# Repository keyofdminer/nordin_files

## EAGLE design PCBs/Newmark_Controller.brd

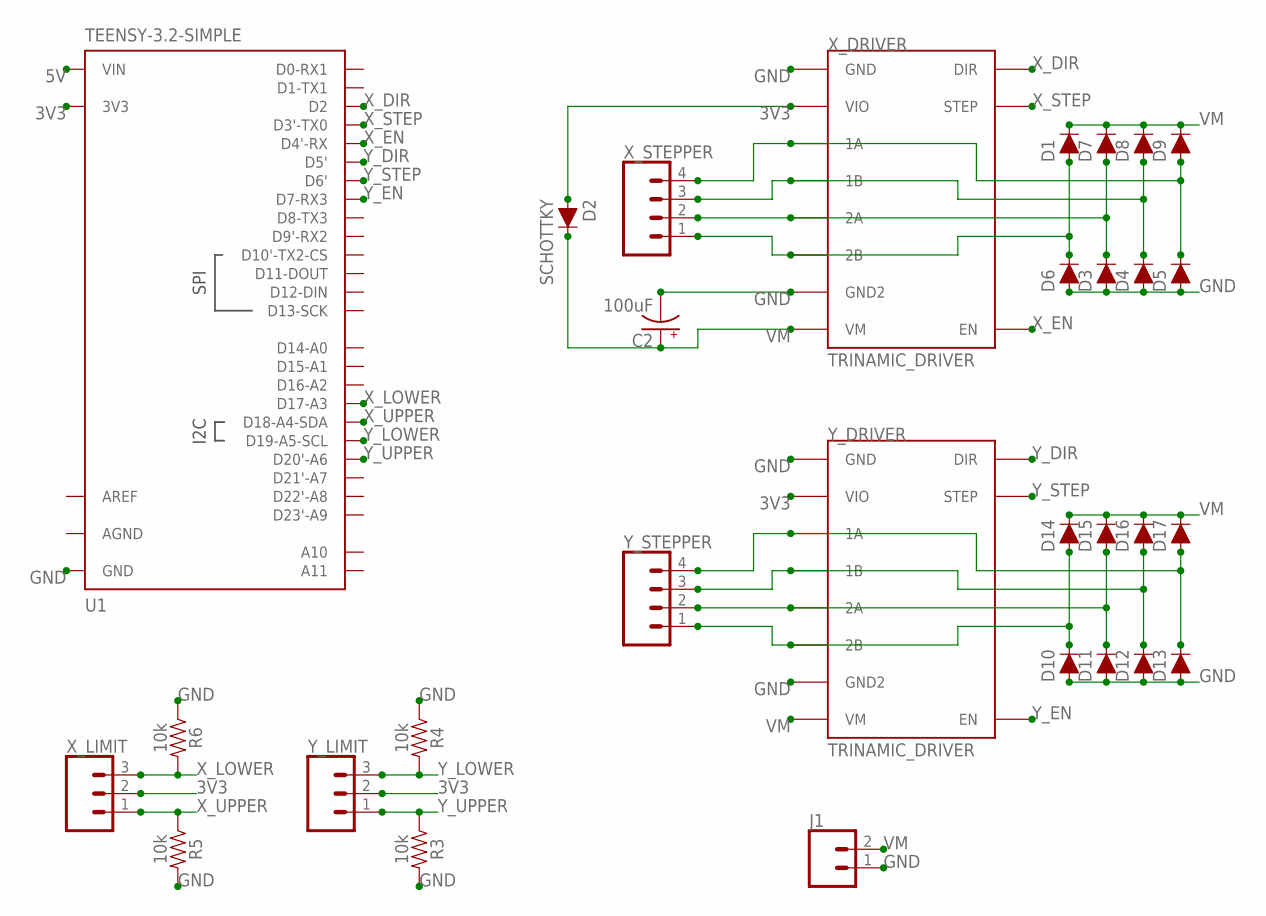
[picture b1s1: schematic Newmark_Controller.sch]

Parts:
C2: 100uF; CPOL-RADIAL-2.5MM-6.5MM
D1, D3, D4, D5, D6, D7, D8, D9, D10, D11, D12, D13, D14, D15, D16, D17: DIODE-1N4148
D2: SCHOTTKY; DIODE-1N4148
J1: CONN_023.5MM; SCREWTERMINAL-3.5MM-2
R3, R4, R5, R6: 10k; AXIAL-0.3
U1: TEENSY-3.2-SIMPLE
X_DRIVER: TRINAMIC_DRIVER
X_LIMIT: CONN_03; 1X03
X_STEPPER: CONN_04PTH; 1X04
Y_DRIVER: TRINAMIC_DRIVER
Y_LIMIT: CONN_03; 1X03
Y_STEPPER: CONN_04PTH; 1X04

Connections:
3V3: D2.A, U1.3.3V (3V3), X_DRIVER.5V (VIO), X_LIMIT.2, Y_DRIVER.5V (VIO), Y_LIMIT.2
5V: U1.VIN
AGND: U1.AGND
AREF: U1.AREF
GND: C2.2 (-), D3.A, D4.A, D5.A, D6.A, D10.A, D11.A, D12.A, D13.A, J1.1, R3.P$2 (2), R4.P$1 (1), R5.P$2 (2), R6.P$1 (1), U1.GND, X_DRIVER.GND, X_DRIVER.GND2, Y_DRIVER.GND, Y_DRIVER.GND2
unnamed: D5.C, D9.A, X_DRIVER.1A, X_STEPPER.4
unnamed: D4.C, D8.A, X_DRIVER.1B, X_STEPPER.3
unnamed: D3.C, D7.A, X_DRIVER.2A, X_STEPPER.2
unnamed: D1.A, D6.C, X_DRIVER.2B, X_STEPPER.1
unnamed: D13.C, D17.A, Y_DRIVER.1A, Y_STEPPER.4
unnamed: D12.C, D16.A, Y_DRIVER.1B, Y_STEPPER.3
unnamed: D11.C, D15.A, Y_DRIVER.2A, Y_STEPPER.2
unnamed: D10.C, D14.A, Y_DRIVER.2B, Y_STEPPER.1
VM: C2.1 (+), D1.C, D2.C, D7.C, D8.C, D9.C, D14.C, D15.C, D16.C, D17.C, J1.2, X_DRIVER.VM, Y_DRIVER.VM
X_DIR: U1.2 (D2), X_DRIVER.DIR
X_EN: U1.4 (D4'-RX), X_DRIVER.EN
X_LOWER: R6.P$2 (2), U1.17 (D17-A3), X_LIMIT.3
X_STEP: U1.3 (D3'-TX0), X_DRIVER.STEP
X_UPPER: R5.P$1 (1), U1.18 (D18-A4-SDA), X_LIMIT.1
Y_DIR: U1.5 (D5'), Y_DRIVER.DIR
Y_EN: U1.7 (D7-RX3), Y_DRIVER.EN
Y_LOWER: R4.P$2 (2), U1.19 (D19-A5-SCL), Y_LIMIT.3
Y_STEP: U1.6 (D6'), Y_DRIVER.STEP
Y_UPPER: R3.P$1 (1), U1.20 (D20'-A6), Y_LIMIT.1

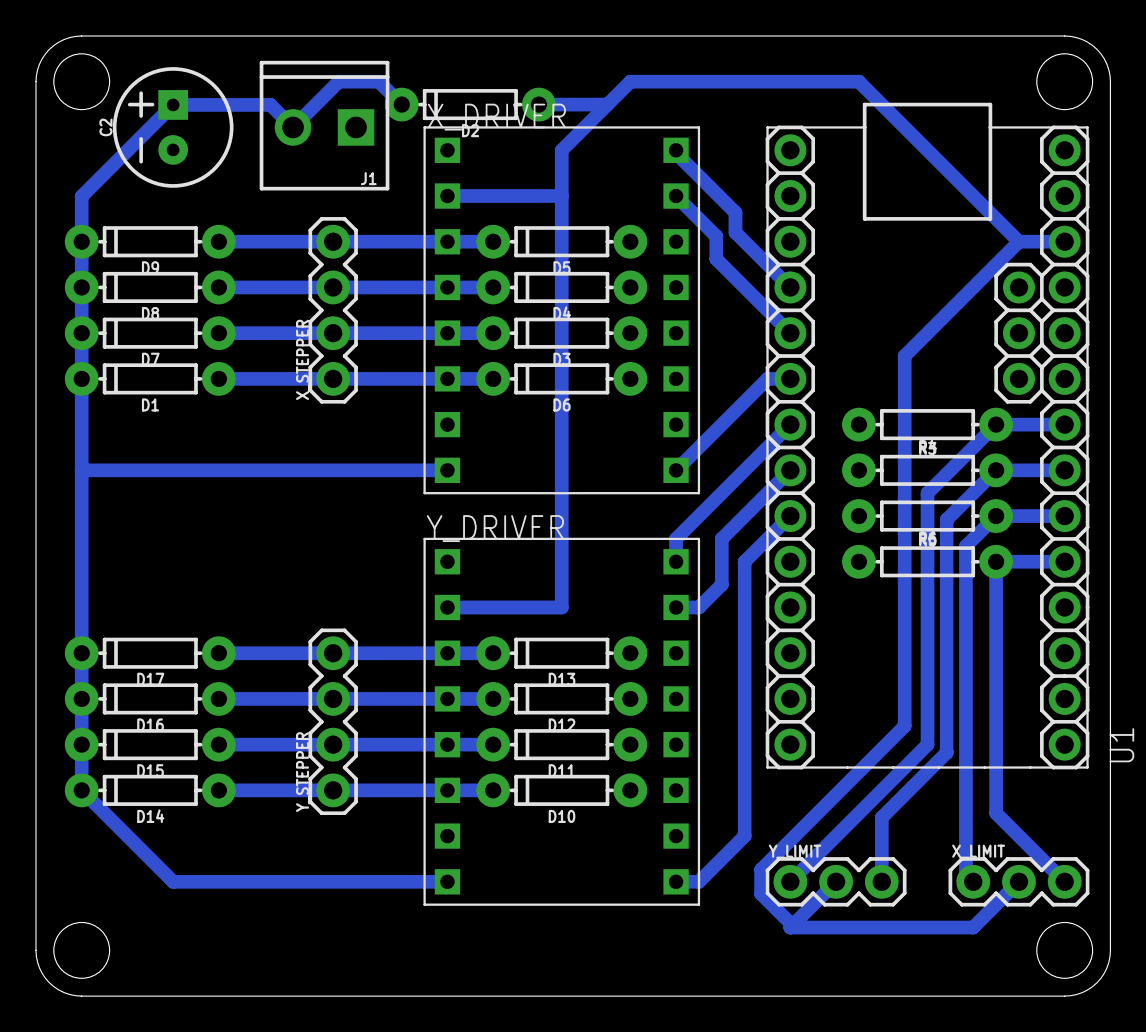
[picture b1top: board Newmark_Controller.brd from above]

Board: 2 copper layers, 59.7 x 53.3 mm, 30 parts (0 on the bottom side), 21 nets.

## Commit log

2020-04-01 Work commit
2020-04-01 Personal commit
2020-04-01 Adding last few work files
2020-04-01 adding last personal file
2020-04-01 worked on calibration box
2020-04-02 worked on power supply at home
2020-04-02 Worked on svg models
2020-04-02 Worked on 3d models
2020-04-02 shopping list
2020-04-02 updated wiring needs
2020-04-02 updated wiring list again...
2020-05-24 Just a update
2020-06-12 Updated the HR3.3 Power supply to have Ethernet instead of I2C
2022-05-02 Update files
2022-05-02 Add files from macbook

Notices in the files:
parts and their libraries:
SparkFun-Connectors: Licensing: Creative Commons ShareAlike 4.0 International - https://creativecommons.org/licenses/by-sa/4.0
